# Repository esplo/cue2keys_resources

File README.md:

# cue2keys_resources

このリポジトリでは、[くっつきー](https://cue2keys.esplo.net/)のドキュメントやその他リソースを保管しています。

ここではくっつきーv2のドキュメントを紹介しています。
[初代くっつきーのドキュメントはこちら](./v1/)をご覧ください。

## くっつきーについて知りたい

[紹介記事](https://www.esplo.net/ja/products/cue2keys2)、[公式サイト](https://cue2keys.esplo.net/)や[ビルドガイド](./v2/docs/build_guide.md)をご覧ください。

## 何を組み合わせればよいか知りたい

[購入ガイド](./v2/docs/shopping_guide.md)をご確認ください。

## 購入したので組み立てを知りたい

[ビルドガイド](./v2/docs/build_guide.md)をご覧ください。

## 感想・不具合報告・要望を伝えたい

[SNS](https://x.com/cue2keys)、[マシュマロ](https://marshmallow-qa.com/9p7qcrd1b86zk8d)、このリポジトリの[issue](https://github.com/esplo/cue2keys_resources/issues)、[BOOTHのメッセージ](https://c2k.booth.pm/)などでご連絡ください。

## 挙動を調整したい

くっつきー2用Webアプリをご利用ください。
利用方法はアプリに記載の案内、[ビルドガイド](./v2/docs/build_guide.md)などをご覧ください。

https://app-cue2keys.esplo.net

## リソース一覧

- [ビルドガイド](./v2/docs/build_guide.md)
- [購入ガイド](./v2/docs/shopping_guide.md)
- [困ったときは？](./v2/docs/troubleshoot.md)

- [初代ユーザー向けガイド](./v2/docs/first_user_guide.md)

- [カスタマイズガイド](./v2/docs/customize_guide.md)
- [ファームウェアガイド](./v2/docs/firmware_guide.md)
- [制限・制約](./v2/docs/limits.md)
- [3Dモデル](./v2/docs/models.md)

モジュールの詳細

- [キーモジュール](./v2/docs/modules/keys.md)
- [ディスプレイモジュール](./v2/docs/modules/display.md)

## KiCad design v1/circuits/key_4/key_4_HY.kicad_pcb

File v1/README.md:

# cue2keys_resources

こちらは初代くっつきーのドキュメントです。
最新版は[こちら](./README.md)をご覧ください。

このリポジトリには、[くっつきー](https://cue2keys.esplo.net/)のドキュメントやその他リソースを保管しています。

## くっつきーについて知りたい

[公式サイト](https://cue2keys.esplo.net/)や[ビルドガイド](./docs/build_guide.md)をご覧ください。

## 何を組み合わせればよいか知りたい

[ビルドガイドの購入ガイド](./docs/build_guide.md)をご確認ください。

## 挙動を調整したい

[カスタムキーコード](./docs/custom_keycodes.md)、[キーマップガイド](./docs/keymap_guide.md)などをご覧ください。

## 不具合報告・要望を伝えたい

各種SNS、[マシュマロ](https://marshmallow-qa.com/9p7qcrd1b86zk8d)、このリポジトリの[issue](https://github.com/esplo/cue2keys_resources/issues)などでご連絡ください。

## リソース一覧

- [3Dモデル](./3D/)
- [ビルドガイド](./docs/build_guide.md)
- [FAQ](./docs/faq.md)
- [カスタマイズガイド](./docs/customize_guide.md)
- [ファームウェアガイド](./docs/firmware_guide.md)
- [キーマッピングガイド](./docs/keymap_guide.md)
- [回路データ](./circuits.md)

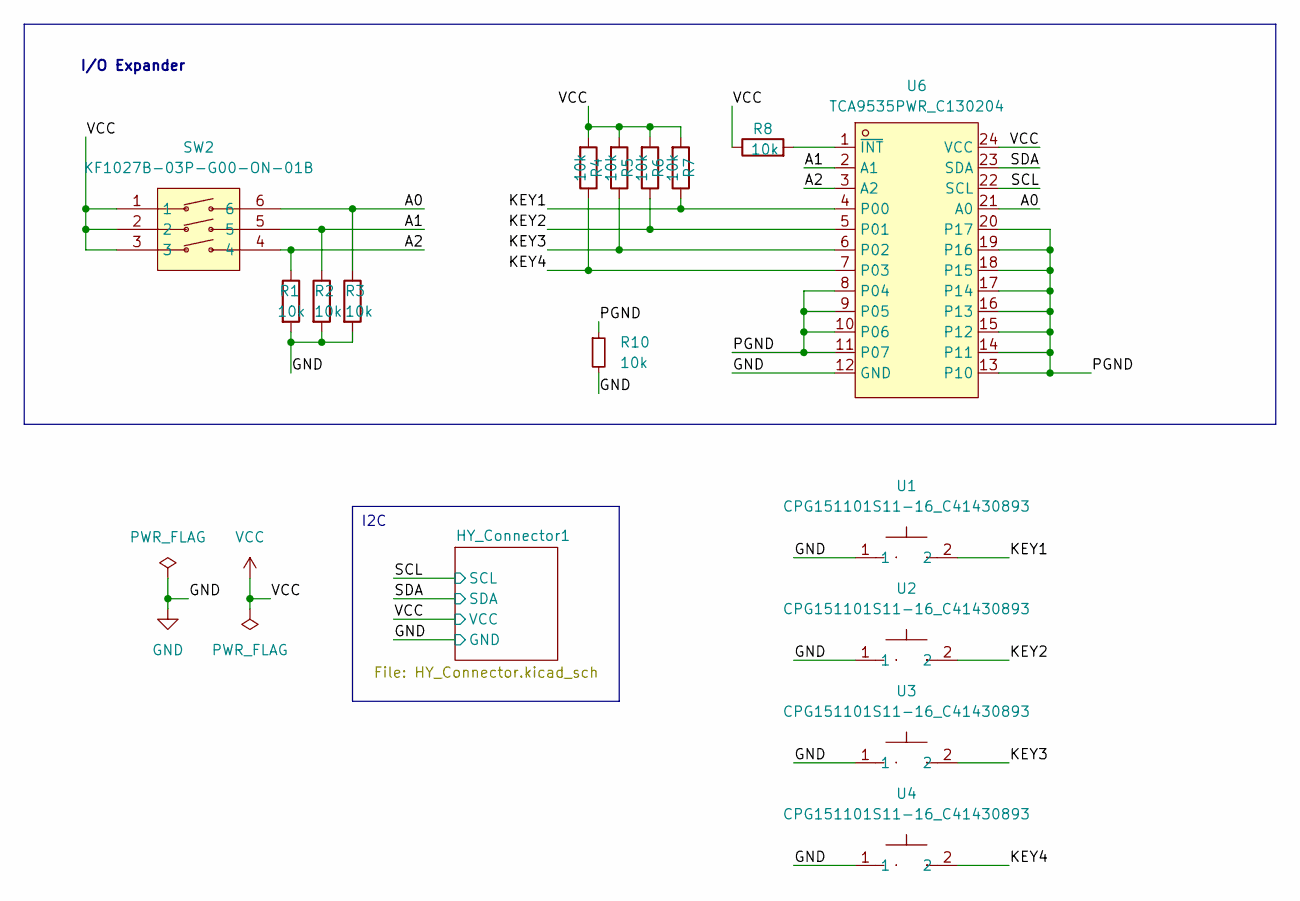
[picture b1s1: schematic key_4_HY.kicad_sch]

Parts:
R1, R2, R3, R4, R5, R6, R7, R8, R10: 10k; R_0805_2012Metric; LCSC Part C17414
SW2: KF1027B-03P-G00-ON-01B; SW-SMD_6P-L8.6-W6.2-P2.54-LS9.9; LCSC Part C976365
U1, U2, U3, U4: CPG151101S11-16_C41430893; SW_Hotswap_Kailh_MX_1.00u; LCSC Part C41430893
U6: TCA9535PWR_C130204; TSSOP-24_L7.8-W4.4-P0.65-LS6.4-BL; LCSC Part C130204

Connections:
/A0: R3.1, SW2.6, U6.21 (A0)
/A1: R2.1, SW2.5, U6.2 (A1)
/A2: R1.1, SW2.4, U6.3 (A2)
/KEY1: R7.1, U1.2, U6.4 (P00)
/KEY2: R6.1, U2.2, U6.5 (P01)
/KEY3: R5.1, U3.2, U6.6 (P02)
/KEY4: R4.1, U4.2, U6.7 (P03)
/PGND: R10.1, U6.8 (P04), U6.9 (P05), U6.10 (P06), U6.11 (P07), U6.13 (P10), U6.14 (P11), U6.15 (P12), U6.16 (P13), U6.17 (P14), U6.18 (P15), U6.19 (P16), U6.20 (P17)
/SCL: U6.22 (SCL); also elsewhere on the board
/SDA: U6.23 (SDA); also elsewhere on the board
GND: R1.2, R2.2, R3.2, R10.2, U1.1, U2.1, U3.1, U4.1, U6.12 (GND); also elsewhere on the board
unnamed: R8.2, U6.1 (~INT)
VCC: R4.2, R5.2, R6.2, R7.2, R8.1, SW2.1, SW2.2, SW2.3, U6.24 (VCC); also elsewhere on the board

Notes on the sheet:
I2C
I/O Expander

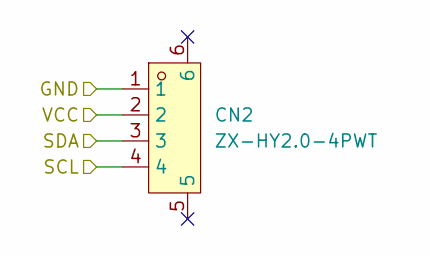
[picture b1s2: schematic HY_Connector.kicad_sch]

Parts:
CN2: ZX-HY2.0-4PWT; CONN-SMD_4P-P2.00_ZX-HY2.0-4PWT; LCSC Part C7429571

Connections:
/SCL: CN2.4; also elsewhere on the board
/SDA: CN2.3; also elsewhere on the board
GND: CN2.1; also elsewhere on the board
VCC: CN2.2; also elsewhere on the board

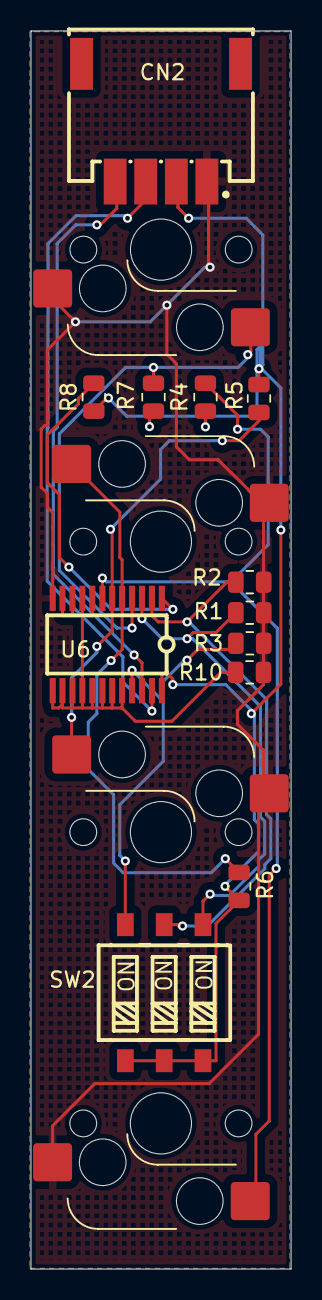
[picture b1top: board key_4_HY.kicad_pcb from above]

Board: 2 copper layers, 17.0 x 81.0 mm, 16 parts (4 on the bottom side), 13 nets.

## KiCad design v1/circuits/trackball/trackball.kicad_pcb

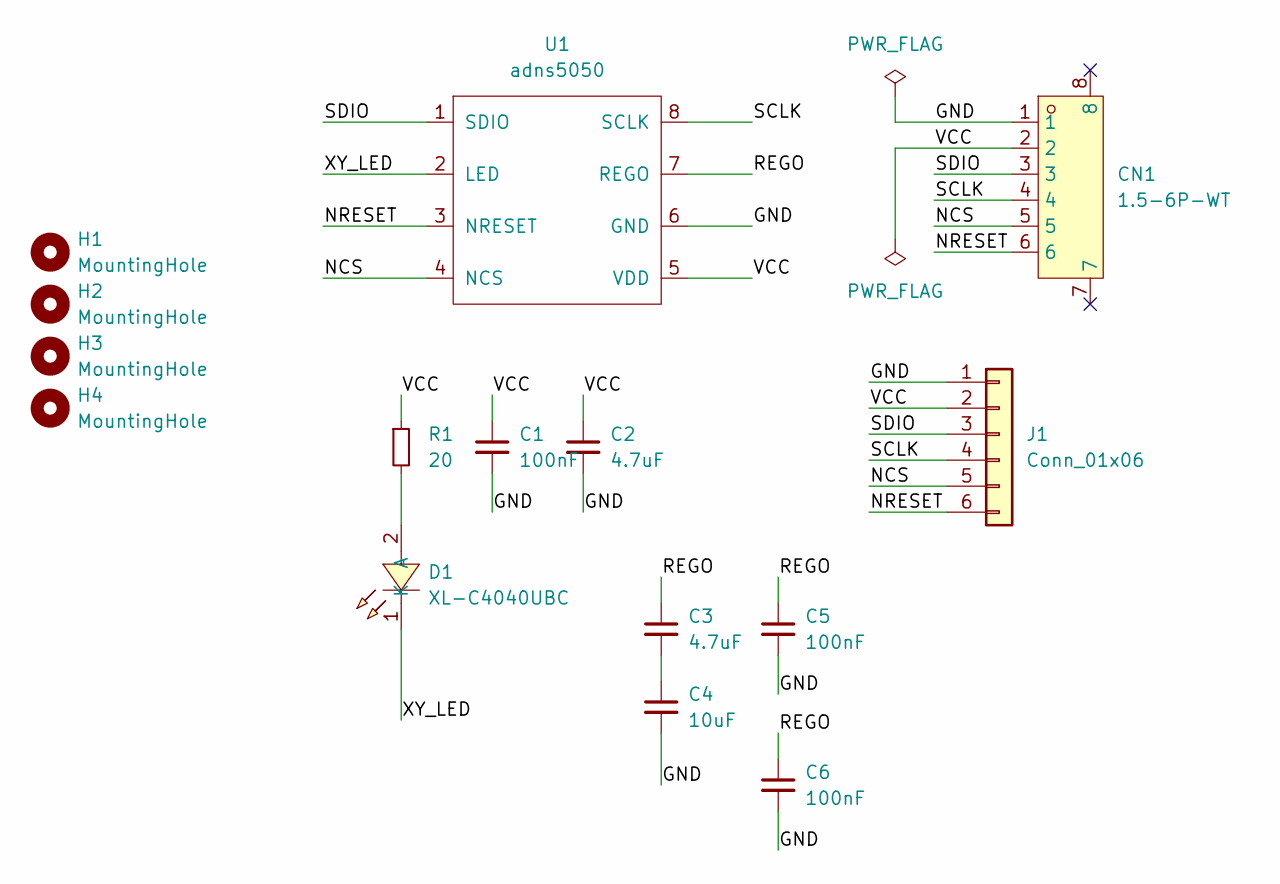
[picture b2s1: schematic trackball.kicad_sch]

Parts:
C1, C5, C6: 100nF; C_0603_1608Metric; LCSC C14663
C2, C3: 4.7uF; C_0603_1608Metric; LCSC C19666
C4: 10uF; C_0603_1608Metric; LCSC C19702
CN1: 1.5-6P-WT; CONN-SMD_1.5-6P-WT; LCSC Part C722672
D1: XL-C4040UBC; LED-SMD_L4.0-W3.6_A67F-U2BA-1-3A4B-30-R33; LCSC Part C7545685
H1, H2, H3, H4: MountingHole; MountingHole_2.5mm
J1: Conn_01x06; PinHeader_1x06_P2.54mm_Vertical
R1: 20; C_0805_2012Metric; LCSC C17544
U1: adns5050; ADNS5050_v2_2

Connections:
/GND: C1.2, C2.2, C4.2, C5.2, C6.2, CN1.1, J1.1, U1.6 (GND)
/NCS: CN1.5, J1.5, U1.4 (NCS)
/NRESET: CN1.6, J1.6, U1.3 (NRESET)
/REGO: C3.1, C5.1, C6.1, U1.7 (REGO)
/SCLK: CN1.4, J1.4, U1.8 (SCLK)
/SDIO: CN1.3, J1.3, U1.1 (SDIO)
/VCC: C1.1, C2.1, CN1.2, J1.2, R1.1, U1.5 (VDD)
/XY_LED: D1.1 (K), U1.2 (LED)
unnamed: C3.2, C4.1
unnamed: D1.2 (A), R1.2

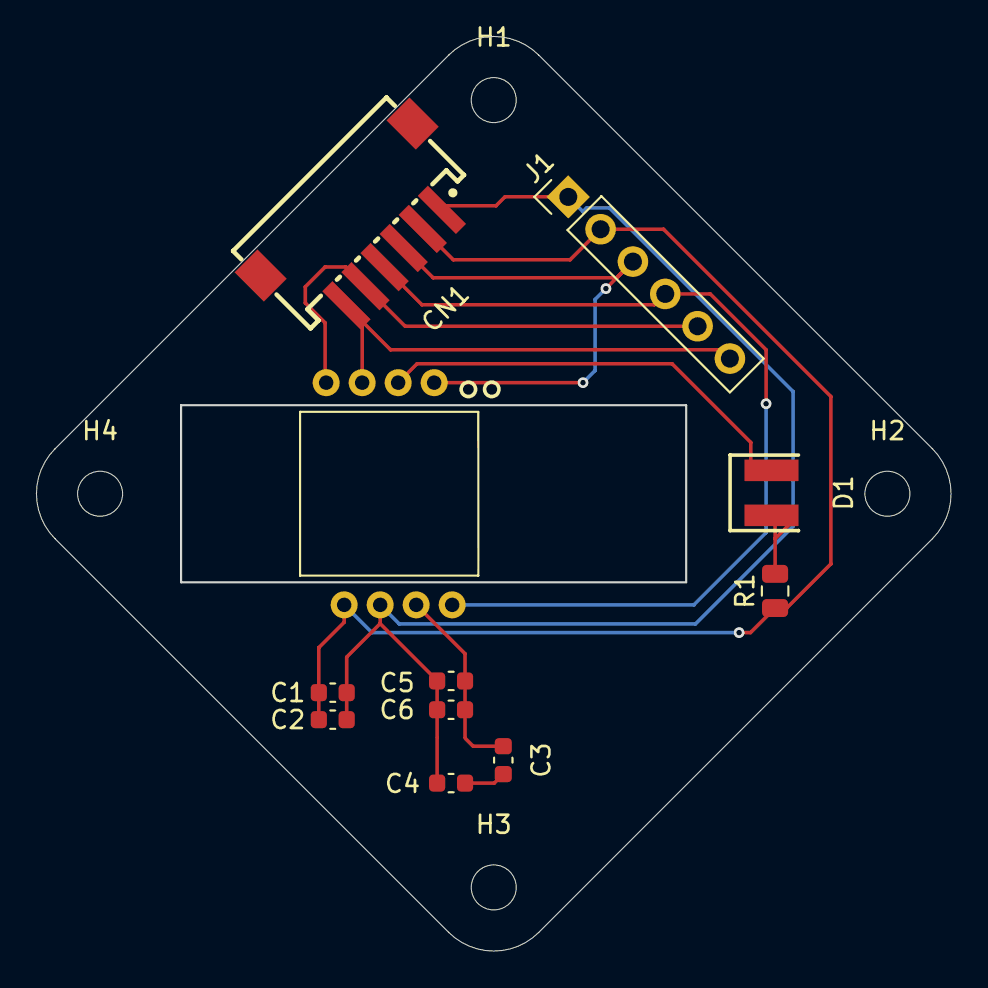
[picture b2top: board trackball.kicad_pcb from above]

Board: 2 copper layers, 50.8 x 50.8 mm, 15 parts (0 on the bottom side), 10 nets.

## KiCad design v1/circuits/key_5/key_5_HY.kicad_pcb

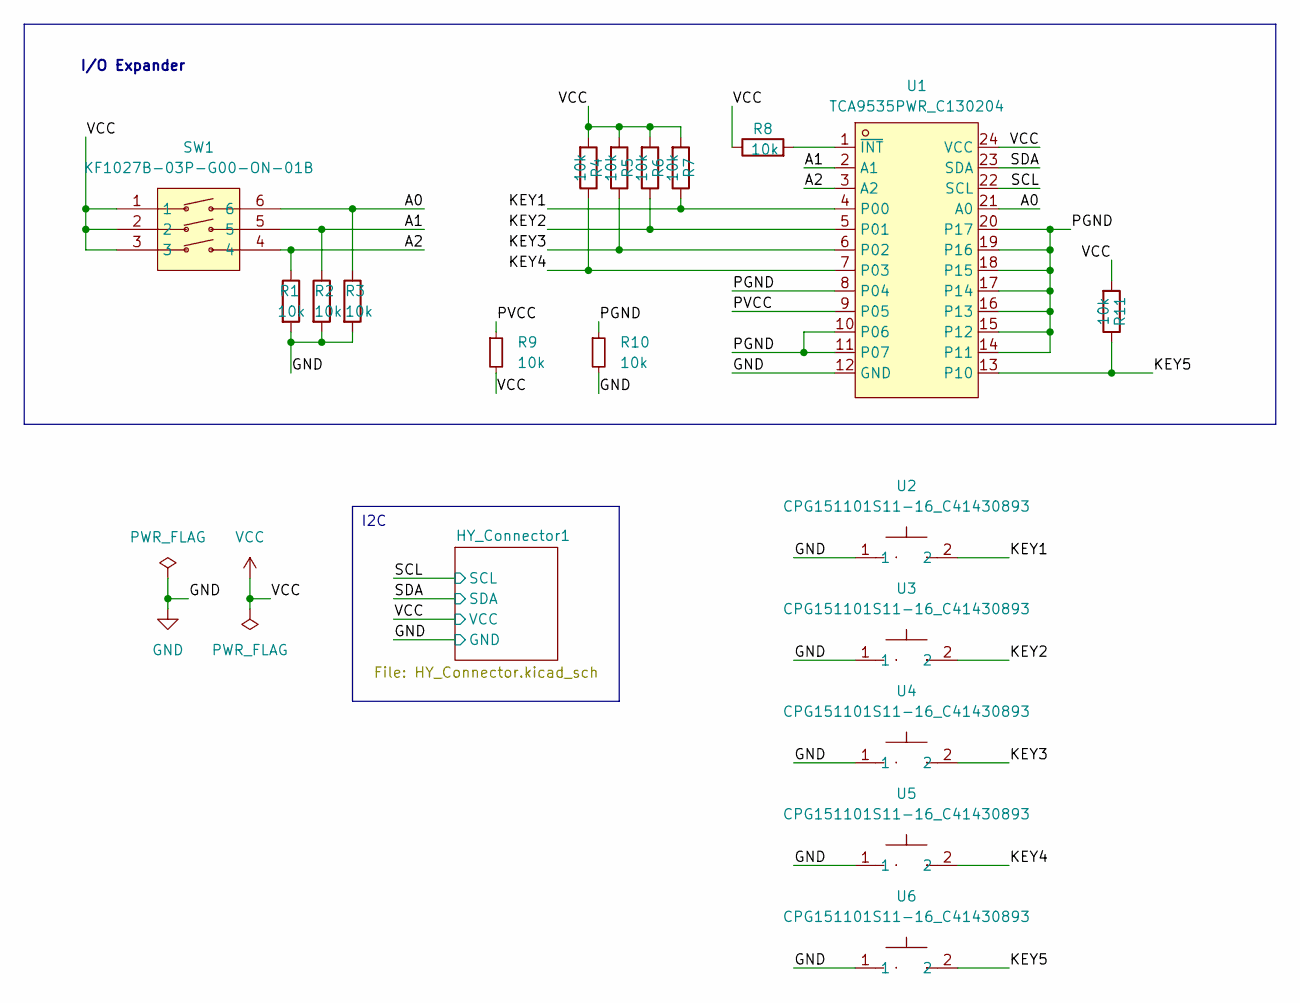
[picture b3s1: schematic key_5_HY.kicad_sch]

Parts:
R1, R2, R3, R4, R5, R6, R7, R8, R9, R10, R11: 10k; R_0805_2012Metric; LCSC Part C17414
SW1: KF1027B-03P-G00-ON-01B; SW-SMD_6P-L8.6-W6.2-P2.54-LS9.9; LCSC Part C976365
U1: TCA9535PWR_C130204; TSSOP-24_L7.8-W4.4-P0.65-LS6.4-BL; LCSC Part C130204
U2, U3, U4, U5, U6: CPG151101S11-16_C41430893; SW_Hotswap_Kailh_MX_1.00u; LCSC Part C41430893

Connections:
/A0: R3.1, SW1.6, U1.21 (A0)
/A1: R2.1, SW1.5, U1.2 (A1)
/A2: R1.1, SW1.4, U1.3 (A2)
/KEY1: R7.1, U1.4 (P00), U2.2
/KEY2: R6.1, U1.5 (P01), U3.2
/KEY3: R5.1, U1.6 (P02), U4.2
/KEY4: R4.1, U1.7 (P03), U5.2
/KEY5: R11.1, U1.13 (P10), U6.2
/PGND: R10.1, U1.8 (P04), U1.10 (P06), U1.11 (P07), U1.14 (P11), U1.15 (P12), U1.16 (P13), U1.17 (P14), U1.18 (P15), U1.19 (P16), U1.20 (P17)
/PVCC: R9.1, U1.9 (P05)
/SCL: U1.22 (SCL); also elsewhere on the board
/SDA: U1.23 (SDA); also elsewhere on the board
GND: R1.2, R2.2, R3.2, R10.2, U1.12 (GND), U2.1, U3.1, U4.1, U5.1, U6.1; also elsewhere on the board
unnamed: R8.2, U1.1 (~INT)
VCC: R4.2, R5.2, R6.2, R7.2, R8.1, R9.2, R11.2, SW1.1, SW1.2, SW1.3, U1.24 (VCC); also elsewhere on the board

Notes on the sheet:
I2C
I/O Expander

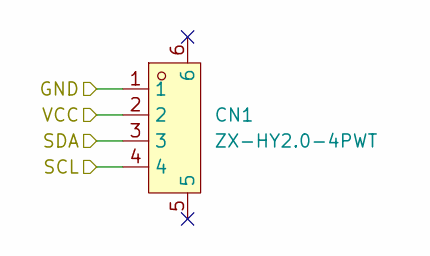
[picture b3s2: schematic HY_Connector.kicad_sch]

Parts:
CN1: ZX-HY2.0-4PWT; CONN-SMD_4P-P2.00_ZX-HY2.0-4PWT; LCSC Part C7429571

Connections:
/SCL: CN1.4; also elsewhere on the board
/SDA: CN1.3; also elsewhere on the board
GND: CN1.1; also elsewhere on the board
VCC: CN1.2; also elsewhere on the board

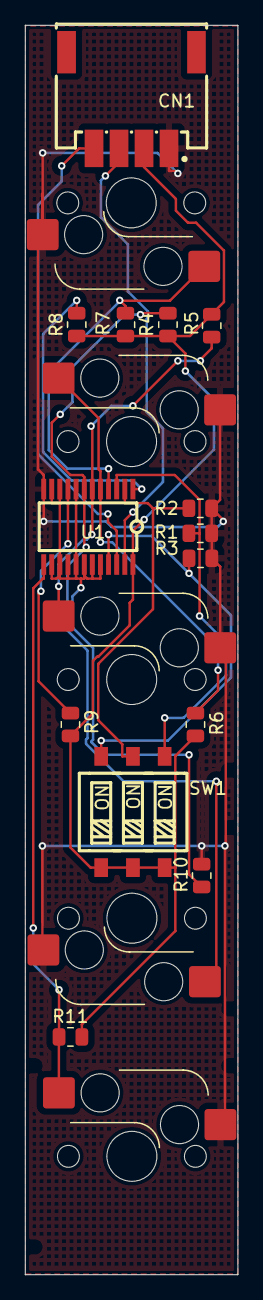
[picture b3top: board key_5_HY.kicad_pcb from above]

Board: 2 copper layers, 17.0 x 100.0 mm, 19 parts (5 on the bottom side), 15 nets.

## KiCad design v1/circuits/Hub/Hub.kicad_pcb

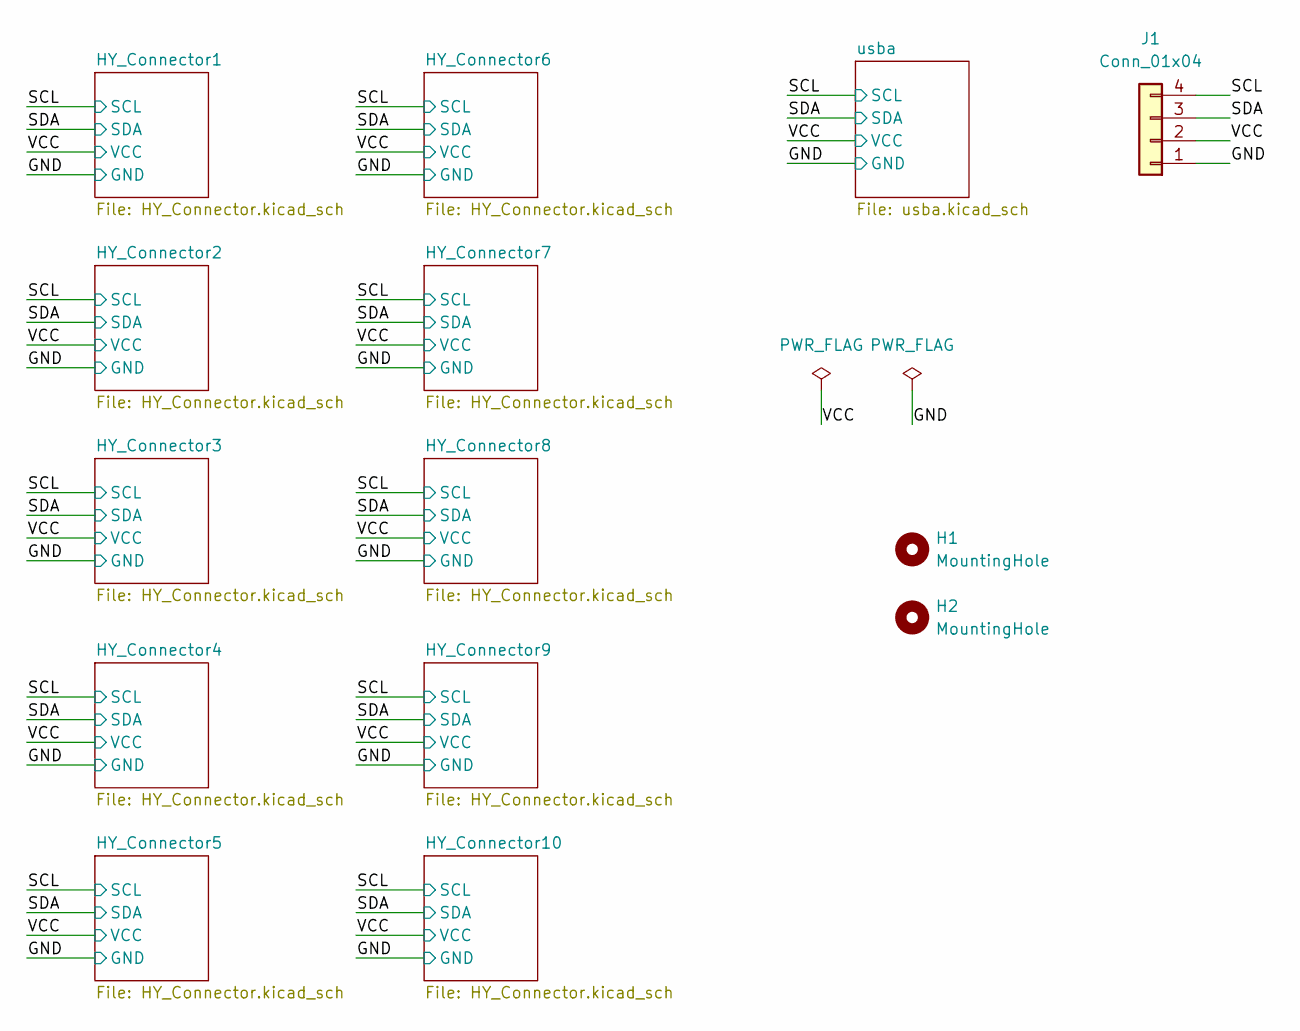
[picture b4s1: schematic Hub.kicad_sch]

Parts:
H1, H2: MountingHole; MountingHole_2.5mm
J1: Conn_01x04; PinHeader_1x04_P2.54mm_Vertical

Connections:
/GND: J1.1; also elsewhere on the board
/SCL: J1.4; also elsewhere on the board
/SDA: J1.3; also elsewhere on the board
/VCC: J1.2; also elsewhere on the board

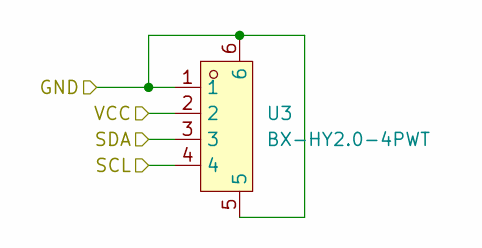
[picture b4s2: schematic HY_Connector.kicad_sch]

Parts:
U3: BX-HY2.0-4PWT; CONN-SMD_4P-P2.0_BX-HY2.0-4PWT; LCSC Part C18077773

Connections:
/GND: U3.1, U3.5, U3.6; also elsewhere on the board
/SCL: U3.4; also elsewhere on the board
/SDA: U3.3; also elsewhere on the board
/VCC: U3.2; also elsewhere on the board

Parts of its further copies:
U1, U2, U4, U5, U6, U7, U8, U9, U10: BX-HY2.0-4PWT; CONN-SMD_4P-P2.0_BX-HY2.0-4PWT; LCSC Part C18077773

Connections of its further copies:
/GND: U1.1, U1.5, U1.6, U2.1, U2.5, U2.6, U4.1, U4.5, U4.6, U5.1, U5.5, U5.6, U6.1, U6.5, U6.6, U7.1, U7.5, U7.6, U8.1, U8.5, U8.6, U9.1, U9.5, U9.6, U10.1, U10.5, U10.6; also elsewhere on the board
/SCL: U1.4, U2.4, U4.4, U5.4, U6.4, U7.4, U8.4, U9.4, U10.4; also elsewhere on the board
/SDA: U1.3, U2.3, U4.3, U5.3, U6.3, U7.3, U8.3, U9.3, U10.3; also elsewhere on the board
/VCC: U1.2, U2.2, U4.2, U5.2, U6.2, U7.2, U8.2, U9.2, U10.2; also elsewhere on the board

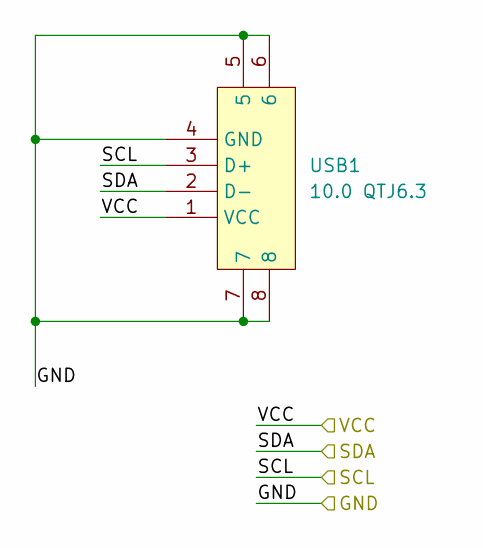
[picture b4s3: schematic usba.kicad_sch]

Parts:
USB1: 10.0 QTJ6.3; USB-A-SMD_10.0-QTJ6.3; LCSC Part C404966

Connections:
/GND: USB1.4 (GND), USB1.5, USB1.6, USB1.7, USB1.8; also elsewhere on the board
/SCL: USB1.3 (D+); also elsewhere on the board
/SDA: USB1.2 (D-); also elsewhere on the board
/VCC: USB1.1 (VCC); also elsewhere on the board

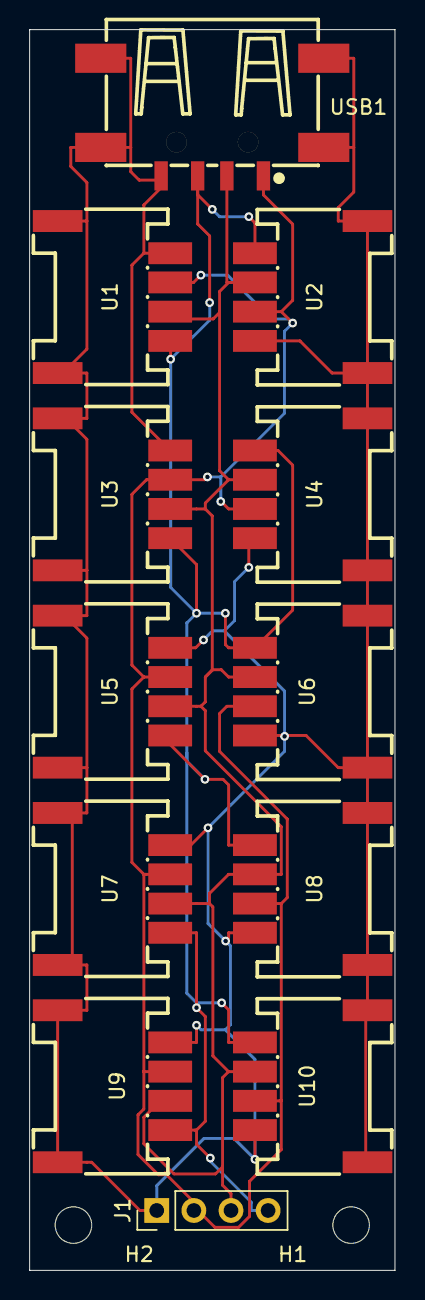
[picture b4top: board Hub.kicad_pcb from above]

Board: 2 copper layers, 25.0 x 84.9 mm, 14 parts (0 on the bottom side), 4 nets.

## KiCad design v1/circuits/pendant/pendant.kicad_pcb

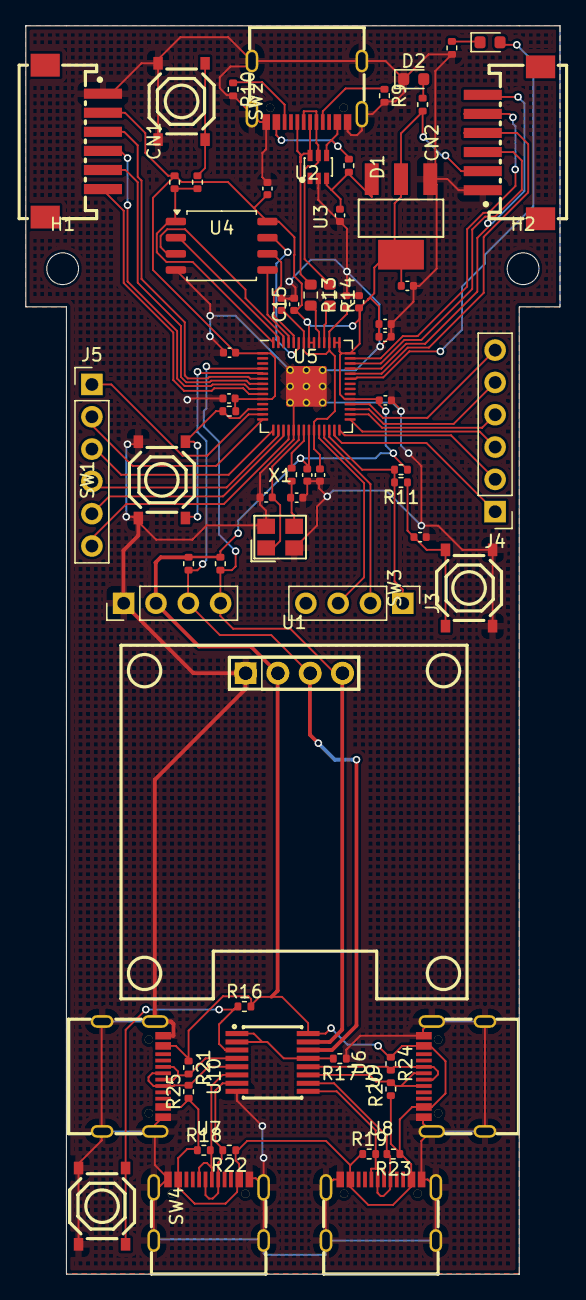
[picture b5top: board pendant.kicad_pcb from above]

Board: 2 copper layers, 42.0 x 98.1 mm, 69 parts (0 on the bottom side), 61 nets.

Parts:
C1, C4: 10u; C_0402_1005Metric
C2, C3: 15p; C_0402_1005Metric
C5, C6, C7, C8, C10, C11, C12, C13, C15, C16, C17: 100n; C_0402_1005Metric
C9, C14: 1u; C_0402_1005Metric
CN1, CN2: 1.5-6P-WT; CONN-SMD_1.5-6P-WT
D1: SMF05CT1G; SOT-363_L2.0-W1.3-P0.65-LS2.1-BR
D2, D3: LED; LED_0603_1608Metric
H1, H2: MountingHole; MountingHole_2.5mm
J1, J2, J3: Conn_01x04; PinHeader_1x04_P2.54mm_Vertical
J4, J5: Conn_01x06; PinHeader_1x06_P2.54mm_Vertical
R1, R6, R8, R12, R16, R17: 10k; R_0402_1005Metric
R2, R3, R5, R7, R11, R15, R18, R19, R20, R21, R22, R23, R24, R25: 1k; R_0402_1005Metric
R4: 0; R_0402_1005Metric
R9, R10: 5.1K; R_0402_1005Metric
R13, R14: 27; R_0603_1608Metric
SW1, SW2, SW3, SW4: TS-1187A-B-A-B; SW-SMD_4P-L5.1-W5.1-P3.70-LS6.5-TL_H1.5
U1: HS96L03W2C03; OLED-TH_L27.8-W27.2-P2.54_C9900033791
U2, U7, U8, U9, U10: GT-USB-7010ASV; USB-C-SMD_G-SWITCH_GT-USB-7010ASV
U3: AMS1117-3.3; SOT-223-3_L6.5-W3.4-P2.30-LS7.0-BR
U4: W25Q128JVS; SOIC-8_5.23x5.23mm_P1.27mm
U5: RP2040; RP2040-QFN-56
U6: PCA9546APW,118; SOP-16_L5.0-W4.4-P0.65-LS6.4-BL
X1: X322512MSB4SI; CRYSTAL-SMD_4P-L3.2-W2.5-BL

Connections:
+1V1: C7.1, C8.1, C9.1, U5.23 (DVDD), U5.45 (VREG_VOUT), U5.50 (DVDD)
+3V3: C4.1, C5.1, C10.1, C11.1, C12.1, C13.1, C14.1, C15.1, C16.1, C17.1, CN1.2, CN2.2, J1.2, J2.2, R1.1, R2.1, R3.1, R6.1, R8.1, R12.1, R16.2, R18.1, R19.1, R20.1, R21.1, R22.1, R23.1, R24.1, R25.1, U1.2 (VCC), U3.2 (VOUT), U3.4 (VOUT), U4.8 (VCC), U5.1 (IOVDD), U5.10 (IOVDD), U5.22 (IOVDD), U5.33 (IOVDD), U5.42 (IOVDD), U5.43 (ADC_AVDD), U5.44 (VREG_IN), U5.48 (USB_VDD), U5.49 (IOVDD), U6.16 (VDD), U7.A4B9 (VBUS), U7.B4A9 (VBUS), U8.A4B9 (VBUS), U8.B4A9 (VBUS), U9.A4B9 (VBUS), U9.B4A9 (VBUS), U10.A4B9 (VBUS), U10.B4A9 (VBUS)
+5V: C1.1, D1.3, R4.2, U3.3 (VIN)
/C1_SPI0_CSn: CN1.5, U5.7 (GPIO5)
/C1_SPI0_RX: CN1.3, U5.6 (GPIO4)
/C1_SPI0_SCK: CN1.4, U5.8 (GPIO6)
/C1_SPI0_TX: CN1.6, U5.9 (GPIO7)
/C1_SPI1_CSn: CN2.5, U5.41 (GPIO29_ADC3)
/C1_SPI1_RX: CN2.3, U5.40 (GPIO28_ADC2)
/C1_SPI1_SCK: CN2.4, U5.38 (GPIO26_ADC0)
/C1_SPI1_TX: CN2.6, U5.39 (GPIO27_ADC1)
/I2CMUX/A2: R17.2, U6.1 (A0), U6.2 (A1), U6.13 (A2)
/I2CMUX/RST: R16.1, SW4.1 (A), SW4.2 (B), U6.3 (/RESET)
/I2CMUX/SC0: R25.2, U6.5 (SC0), U10.A6 (DP1), U10.B6 (DP2)
/I2CMUX/SC1: R22.2, U6.7 (SC1), U7.A6 (DP1), U7.B6 (DP2)
/I2CMUX/SC2: R23.2, U6.10 (SC2), U8.A6 (DP1), U8.B6 (DP2)
/I2CMUX/SC3: R24.2, U6.12 (SC3), U9.A6 (DP1), U9.B6 (DP2)
/I2CMUX/SD0: R21.2, U6.4 (SD0), U10.A7 (DN1), U10.B7 (DN2)
/I2CMUX/SD1: R18.2, U6.6 (SD1), U7.A7 (DN1), U7.B7 (DN2)
/I2CMUX/SD2: R19.2, U6.9 (SD2), U8.A7 (DN1), U8.B7 (DN2)
/I2CMUX/SD3: R20.2, U6.11 (SD3), U9.A7 (DN1), U9.B7 (DN2)
/OLED_SW: R1.2, SW1.3 (C), SW1.4 (D), U5.12 (GPIO9)
/RP2040/GPIO10: J5.1, U5.13 (GPIO10)
/RP2040/GPIO11: J5.2, U5.14 (GPIO11)
/RP2040/GPIO12: J5.3, U5.15 (GPIO12)
/RP2040/GPIO13: J5.4, U5.16 (GPIO13)
/RP2040/GPIO14: J5.5, U5.17 (GPIO14)
/RP2040/GPIO15: J5.6, U5.18 (GPIO15)
/RP2040/GPIO16: J4.1, U5.27 (GPIO16)
/RP2040/GPIO17: J4.2, U5.28 (GPIO17)
/RP2040/GPIO18: J4.3, U5.29 (GPIO18)
/RP2040/GPIO19: J4.4, U5.30 (GPIO19)
/RP2040/GPIO20: J4.5, U5.31 (GPIO20)
/RP2040/GPIO21: J4.6, U5.32 (GPIO21)
/RP2040/LED: D3.2 (A), U5.37 (GPIO25)
/RP2040/QSPI_SCLK: U4.6 (CLK), U5.52 (QSPI_SCLK)
/RP2040/QSPI_SD0: U4.5 (DI(IO0)), U5.53 (QSPI_SD0)
/RP2040/QSPI_SD1: U4.2 (DO(IO1)), U5.55 (QSPI_SD1)
/RP2040/QSPI_SD2: U4.3 (IO2), U5.54 (QSPI_SD2)
/RP2040/QSPI_SD3: U4.7 (IO3), U5.51 (QSPI_SD3)
/RP2040/QSPI_SS: R5.1, R6.2, U4.1 (~CS), U5.56 (QSPI_SS)
/RP2040/RUN: J3.1, R11.2, R12.2, U5.26 (RUN)
/RP2040/SWCLK: J3.3, U5.24 (SWCLK)
/RP2040/SWD: J3.2, U5.25 (SWD)
/RP2040/USB_D+: D1.6, R13.1, U2.A6 (DP1), U2.B6 (DP2)
/RP2040/USB_D-: D1.5, R14.1, U2.A7 (DN1), U2.B7 (DN2)
/RP2040/VBUS: D1.4, R4.1, U2.A4B9 (VBUS), U2.B4A9 (VBUS)
/RP2040/XIN: C2.1, U5.20 (XIN), X1.1 (OSC1)
/RP2040/XOUT: R7.1, U5.21 (XOUT)
/RP2040/~USB_BOOT: R5.2, SW2.1 (A), SW2.2 (B)
/SCL: J1.3, J2.3, R2.2, U1.3 (SCL), U5.5 (GPIO3), U6.14 (SCL)
/SDA: J1.4, J2.4, R3.2, U1.4 (SDA), U5.4 (GPIO2), U6.15 (SDA)
GND: C1.2, C2.2, C3.2, C4.2, C5.2, C6.2, C7.2, C8.2, C9.2, C10.2, C11.2, C12.2, C13.2, C14.2, C15.2, C16.2, C17.2, CN1.1, CN2.1, D1.2, D2.1 (K), J1.1, J2.1, R9.2, R10.2, R15.2, R17.1, SW1.1 (A), SW1.2 (B), SW2.3 (C), SW2.4 (D), SW3.3 (C), SW3.4 (D), SW4.3 (C), SW4.4 (D), U1.1 (GND), U2.1 (SHELL), U2.2 (SHELL), U2.3 (SHELL), U2.4 (SHELL), U2.A1B12 (GND), U2.B1A12 (GND), U3.1 (GND), U4.4 (GND), U5.19 (TESTEN), U5.57 (GND), U6.8 (VSS), U7.1 (SHELL), U7.2 (SHELL), U7.3 (SHELL), U7.4 (SHELL), U7.A1B12 (GND), U7.B1A12 (GND), U8.1 (SHELL), U8.2 (SHELL), U8.3 (SHELL), U8.4 (SHELL), U8.A1B12 (GND), U8.B1A12 (GND), U9.1 (SHELL), U9.2 (SHELL), U9.3 (SHELL), U9.4 (SHELL), U9.A1B12 (GND), U9.B1A12 (GND), U10.1 (SHELL), U10.2 (SHELL), U10.3 (SHELL), U10.4 (SHELL), U10.A1B12 (GND), U10.B1A12 (GND), X1.2 (GND), X1.4 (GND)
unnamed: D2.2 (A), R8.2
unnamed: D3.1 (K), R15.1
unnamed: C6.1, R11.1, SW3.1 (A), SW3.2 (B)
unnamed: R9.1, U2.A5 (CC1)
unnamed: R10.1, U2.B5 (CC2)
unnamed: R14.2, U5.46 (USB_DM)
unnamed: R13.2, U5.47 (USB_DP)
unnamed: C3.1, R7.2, X1.3 (OSC2)

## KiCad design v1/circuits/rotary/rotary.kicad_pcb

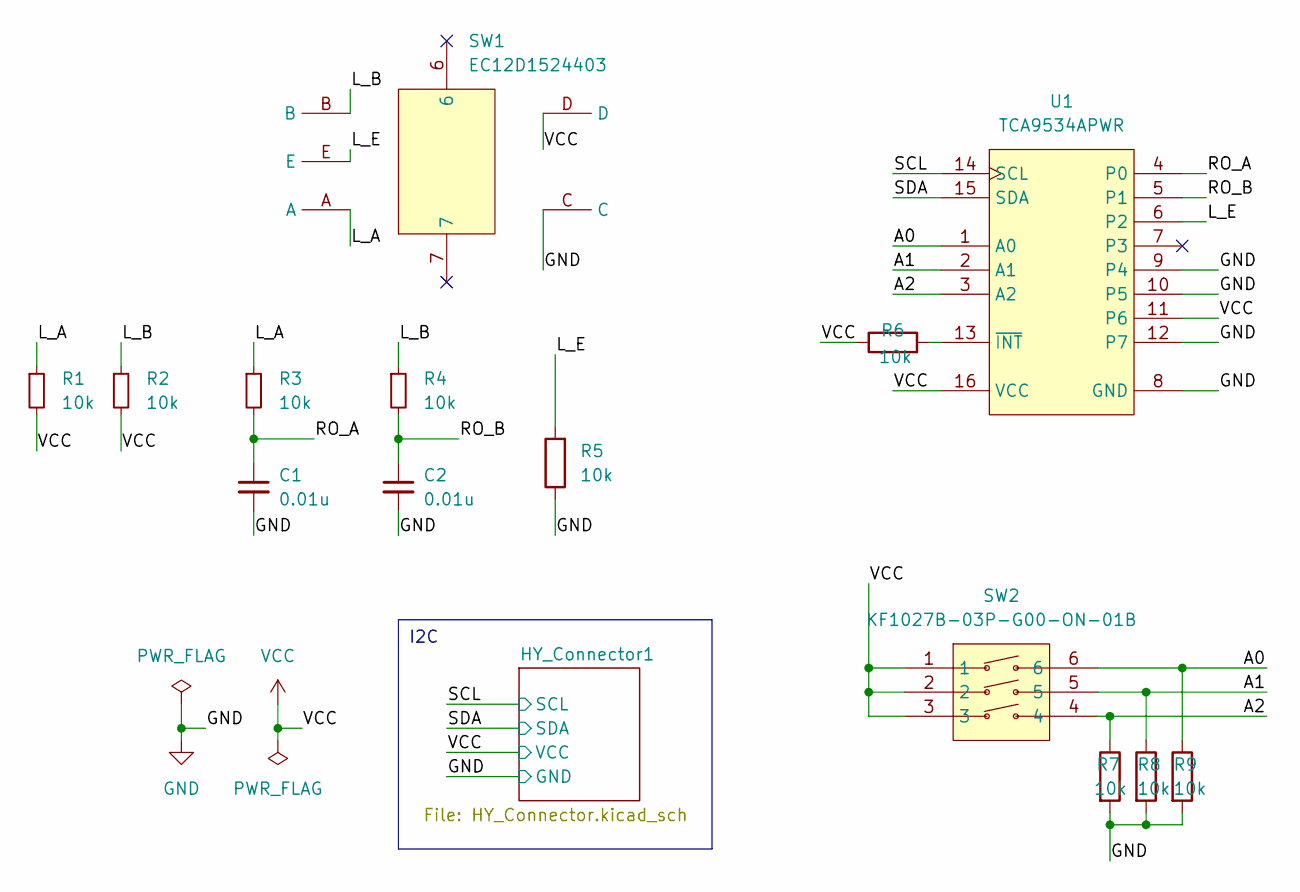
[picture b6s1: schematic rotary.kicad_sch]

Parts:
C1, C2: 0.01u; C_0402_1005Metric; LCSC Part C15195
R1, R2, R3, R4, R5, R6, R7, R8, R9: 10k; R_0402_1005Metric; LCSC Part C17414
SW1: EC12D1524403; SW-TH_EC12D1524403; LCSC Part C112349
SW2: KF1027B-03P-G00-ON-01B; SW-SMD_6P-L8.6-W6.2-P2.54-LS9.9; LCSC Part C976365
U1: TCA9534APWR; TSSOP-16_L5.0-W4.4-P0.65-LS6.4-BL; LCSC Part C206010

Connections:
/A0: R9.1, SW2.6, U1.1 (A0)
/A1: R8.1, SW2.5, U1.2 (A1)
/A2: R7.1, SW2.4, U1.3 (A2)
/L_A: R1.1, R3.1, SW1.A
/L_B: R2.1, R4.1, SW1.B
/L_E: R5.2, SW1.E, U1.6 (P2)
/RO_A: C1.1, R3.2, U1.4 (P0)
/RO_B: C2.1, R4.2, U1.5 (P1)
/SCL: U1.14 (SCL); also elsewhere on the board
/SDA: U1.15 (SDA); also elsewhere on the board
GND: C1.2, C2.2, R5.1, R7.2, R8.2, R9.2, SW1.C, U1.8 (GND), U1.9 (P4), U1.10 (P5), U1.12 (P7); also elsewhere on the board
unnamed: R6.2, U1.13 (~INT)
VCC: R1.2, R2.2, R6.1, SW1.D, SW2.1, SW2.2, SW2.3, U1.11 (P6), U1.16 (VCC); also elsewhere on the board

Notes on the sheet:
I2C

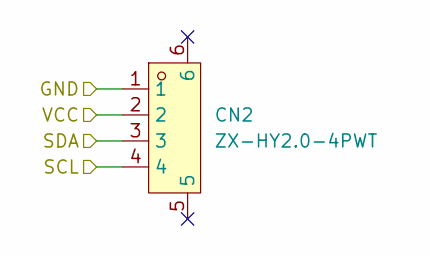
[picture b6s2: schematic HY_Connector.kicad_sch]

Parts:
CN2: ZX-HY2.0-4PWT; CONN-SMD_4P-P2.00_ZX-HY2.0-4PWT; LCSC Part C7429571

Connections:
/SCL: CN2.4; also elsewhere on the board
/SDA: CN2.3; also elsewhere on the board
GND: CN2.1; also elsewhere on the board
VCC: CN2.2; also elsewhere on the board

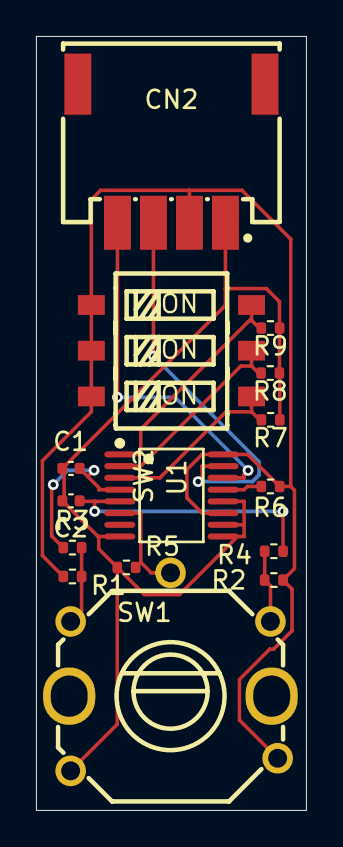
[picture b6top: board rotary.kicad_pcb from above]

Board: 2 copper layers, 15.0 x 43.0 mm, 15 parts (0 on the bottom side), 13 nets.

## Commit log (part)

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2025-03-11 Add tiny descriptions to build_guide.md
2025-03-12 update firmware and corresponding docs
2025-03-20 add 3D model data
2025-03-23 new firmware: modify mouse delay settings
2025-03-23 add remap save feature note
2025-03-23 update firmware document
2025-03-23 fix typo
2025-03-23 fix minor wording
2025-03-24 update keymap guide
2025-03-27 fix via.json for encoders
2025-03-29 firmware update: add drag scroll feature
2025-04-18 add latest firmware
2025-04-18 add custom keycode doc
2025-04-18 add set guide
2025-04-18 minor updates
2025-04-18 update firmware guide
2025-04-19 minor update: doc refactoring
2026-03-25 update to v2
2026-03-25 fix: add background to `thinking` image
2026-03-25 add booth links
2026-03-25 minor fix
2026-03-29 Update README with build guide and contact info
2026-03-31 Update build guide with assembly details and tips
    Added details about starter set components and cable management for assembly.
2026-03-31 Update build guide with assembly details and tips (#27)
    Added details about starter set components and cable management for assembly.
2026-03-31 add online shopping in shopping guide
2026-03-31 add online shopping in shopping guide (#28)
2026-06-26 add 3D models
2026-06-26 add 3D models (#29)
